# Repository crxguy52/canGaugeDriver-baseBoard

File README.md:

Hardware to to use [CANBed FD](https://www.seeedstudio.com/CANBed-FD-Arduino-CAN-FD-Development-Kit-p-4724.html) to read CAN data and drive gauges on a NB Miata

Used in conjunction with the [software](https://github.com/crxguy52/canGaugeDriver)

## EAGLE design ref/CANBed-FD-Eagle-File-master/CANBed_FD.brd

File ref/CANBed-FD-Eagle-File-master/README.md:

# CANBed-FD-Eagle-File
EAGLE FILE FOR CANBED-FD

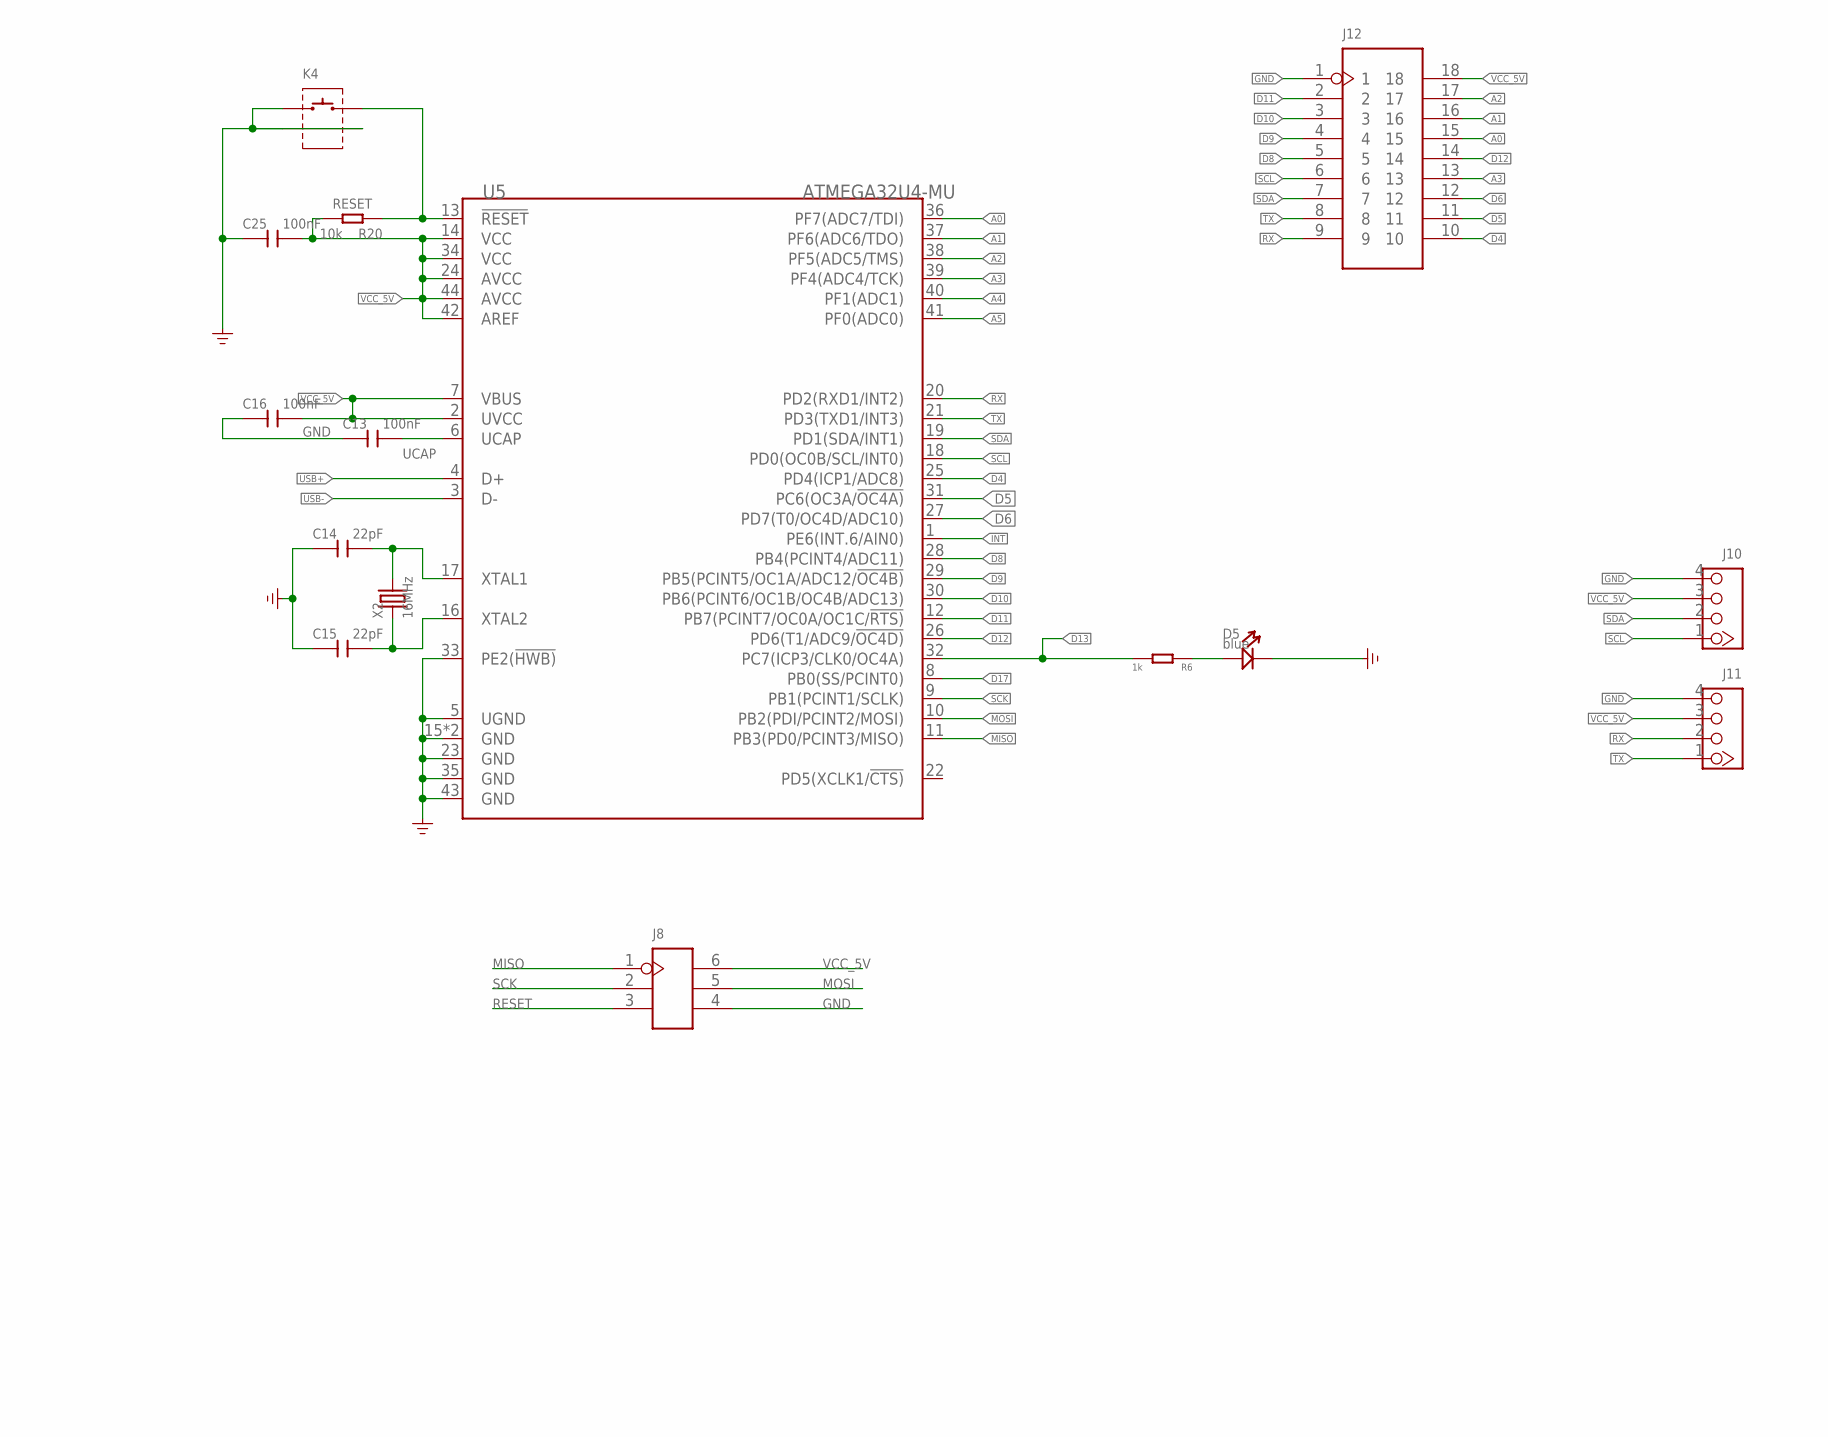
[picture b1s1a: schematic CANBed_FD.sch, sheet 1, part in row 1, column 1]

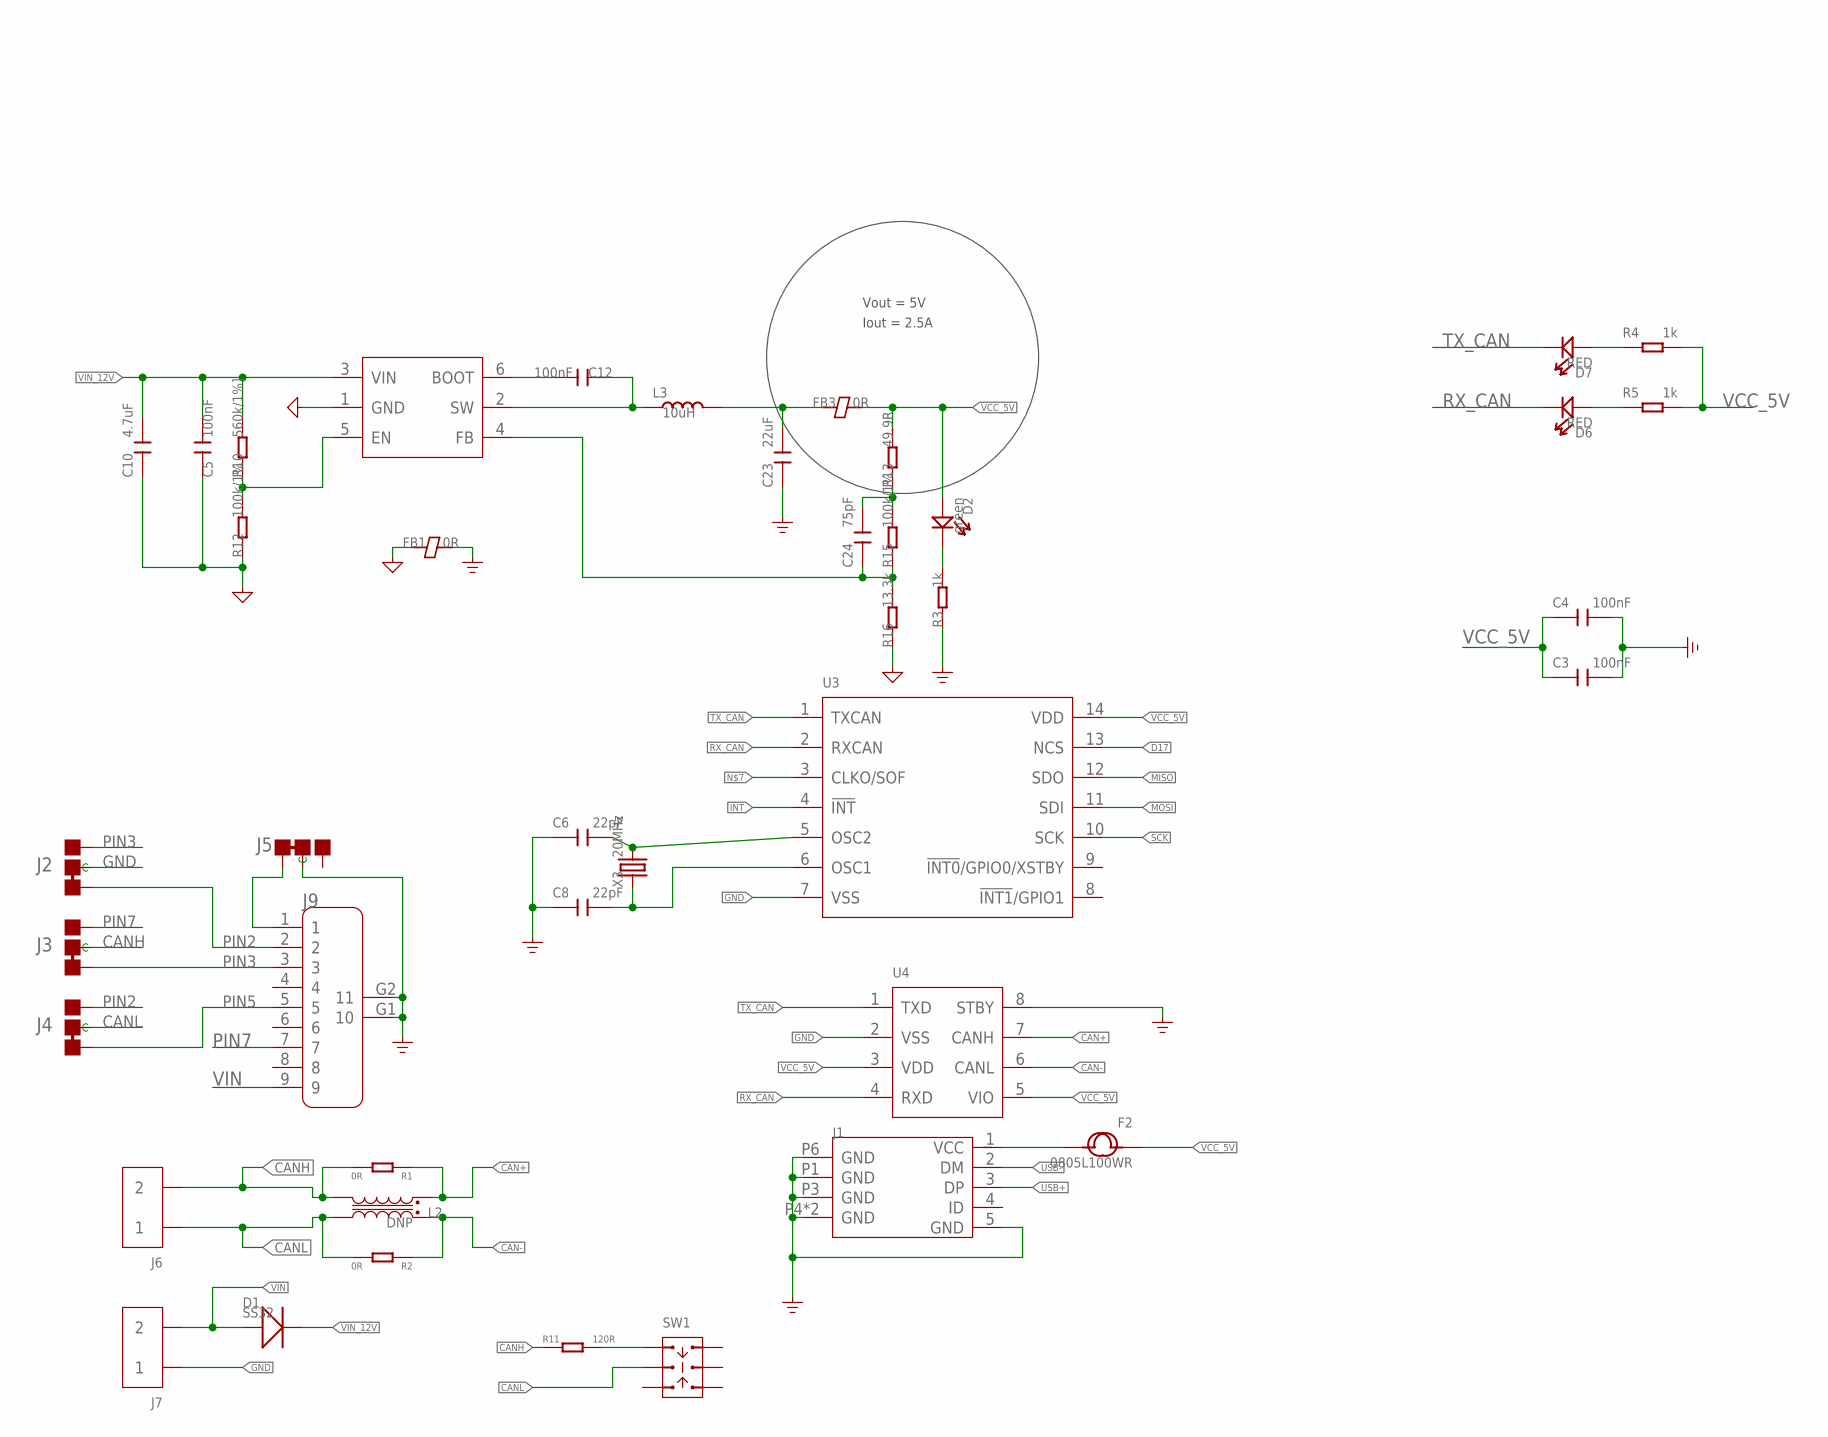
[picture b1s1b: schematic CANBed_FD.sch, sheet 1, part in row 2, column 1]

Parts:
C3, C4, C5, C12, C13, C16, C25: 100nF; C0603
C6, C8, C14, C15: 22pF; C0603
C10: 4.7uF; C1206
C23: 22uF; C1206
C24: 75pF; C0603
D1: SS32; DO-214AC
D2: green; LED-0603
D5: blue; LED-0603
D6, D7: RED; LED-0603
F2: 0805L100WR; F0805
FB1, FB3: 0R; F0805
J1: MICRO-USB5+4P-320010050; MICRO-USB5+5P-SMD-0.65-7.2X5.06MM
J2, J3, J4, J5: JUMPER-3P-SHORT; 3P-SMD-SHORT
J6, J7: SCREW-TERMINAL-2P'5.08'; H2-5.0-10.5X8.0MM
J8: HEADER-2X3P-2.54; H2X3-2.54
J9: DB9'MEAL'; DB9-MEAL
J10, J11: 320110033; HW4-2.0
J12: HEADER-2X9P-2.54; H2X9-2.54
K4: BUTTON-2+2P; SW2+2P-7.7X2.75X3.95MM
L2: DNP; INT4-0.85-2X1.25X1.2MM
L3: 10uH; INT2-SMD-6.6X7.1X3MM
R1, R2: 0R; R0603
R3, R4, R5, R6: 1k; R0603
R10: 560k/1%]; R0603
R11: 120R; R0603
R12, R15: 100k/1%; R0603
R13: 49.9R; R0603
R16: 13.3k; R0603
R20: 10k; R0603
SW1: SWITCH-2CH-6P-311010004; SW6-2.54-9.0X3.5X3.2+2.0MM
U3: CONTROLLER-MCP2517FD; SOIC14-1.27-8.6X3.9MM
U4: TRANSCEIVER-MCP2542; SOIC8-1.27-5X4MM
U5: ATMEGA32U4-MU; QFN44
U$11: PMIC-TPS54302; SOT-23-6
X2: 16MHz; HC49US
X3: 20MHz; HC49US

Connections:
A0: J12.15, U5.36 (PF7(ADC7/TDI))
A1: J12.16, U5.37 (PF6(ADC6/TDO))
A2: J12.17, U5.38 (PF5(ADC5/TMS))
A3: J12.13, U5.39 (PF4(ADC4/TCK))
A4: U5.40 (PF1(ADC1))
A5: U5.41 (PF0(ADC0))
AGND: C5.1, C10.1, FB1.1, R12.1, R16.1, U$11.1 (GND)
CAN+: L2.4, R1.1, U4.7 (CANH)
CAN-: L2.1, R2.1, U4.6 (CANL)
CANH: J3.MM (C), J6.2, L2.3, R1.2, R11.1
CANL: J4.MM (C), J6.1, L2.2, R2.2, SW1.COM1
D4: J12.10, U5.25 (PD4(ICP1/ADC8))
D5: J12.11, U5.31 (PC6(OC3A/!OC4A))
D6: J12.12, U5.27 (PD7(T0/OC4D/ADC10))
D8: J12.5, U5.28 (PB4(PCINT4/ADC11))
D9: J12.4, U5.29 (PB5(PCINT5/OC1A/ADC12/!OC4B))
D10: J12.3, U5.30 (PB6(PCINT6/OC1B/OC4B/ADC13))
D11: J12.2, U5.12 (PB7(PCINT7/OC0A/OC1C/!RTS))
D12: J12.14, U5.26 (PD6(T1/ADC9/!OC4D))
D13: R6.2, U5.32 (PC7(ICP3/CLK0/OC4A))
D17: U3.13 (NCS), U5.8 (PB0(SS/PCINT0))
EXT_PWR: F2.2, J1.1 (VCC)
GND: C3.2, C4.2, C6.1, C8.1, C13.1, C14.1, C15.1, C16.1, C23.1, C25.1, D5.-, FB1.2, J1.5 (GND), J1.P1 (GND), J1.P3 (GND), J1.P4 (GND), J1.P5 (GND), J1.P6 (GND), J2.MM (C), J5.MM (C), J7.1, J8.4, J9.G1 (10), J9.G2 (11), J10.4, J11.4, J12.1, K4.1, K4.S1, K4.S2, R3.1, U3.7 (VSS), U4.2 (VSS), U4.8 (STBY), U5.5 (UGND), U5.15 (GND), U5.23 (GND), U5.33 (PE2(!HWB)), U5.35 (GND), U5.43 (GND), U5.TAB (GND)
INT: U3.4 (!INT), U5.1 (PE6(INT.6/AIN0))
MISO: J8.1, U3.12 (SDO), U5.11 (PB3(PD0/PCINT3/MISO))
MOSI: J8.5, U3.11 (SDI), U5.10 (PB2(PDI/PCINT2/MOSI))
unnamed: D2.-, R3.2
unnamed: D7.+, R4.1
unnamed: R10.1, R12.2, U$11.5 (EN)
unnamed: C14.2, U5.17 (XTAL1), X2.2
unnamed: D5.+, R6.1
unnamed: C6.2, U3.5 (OSC2), X3.2
unnamed: C12.1, L3.1, U$11.2 (SW)
unnamed: C15.2, U5.16 (XTAL2), X2.1
unnamed: J5.11 (L), J9.1
unnamed: C12.2, U$11.6 (BOOT)
unnamed: D6.+, R5.1
unnamed: R11.2, SW1.CH1A
unnamed: C8.2, U3.6 (OSC1), X3.1
unnamed: C23.2, FB3.1, L3.2
unnamed: C24.2, R13.1, R15.2
unnamed: C24.1, R15.1, R16.2, U$11.4 (FB)
PIN2: J2.11 (L), J4.00 (R), J9.2
PIN3: J2.00 (R), J3.11 (L), J9.3
PIN5: J4.11 (L), J9.5
PIN7: J3.00 (R), J9.7
RESET: J8.3, K4.2, R20.1, U5.13 (!RESET)
RX: J11.2, J12.9, U5.20 (PD2(RXD1/INT2))
RX_CAN: D6.-, U3.2 (RXCAN), U4.4 (RXD)
SCK: J8.2, U3.10 (SCK), U5.9 (PB1(PCINT1/SCLK))
SCL: J10.1, J12.6, U5.18 (PD0(OC0B/SCL/INT0))
SDA: J10.2, J12.7, U5.19 (PD1(SDA/INT1))
TX: J11.1, J12.8, U5.21 (PD3(TXD1/INT3))
TX_CAN: D7.-, U3.1 (TXCAN), U4.1 (TXD)
UCAP: C13.2, U5.6 (UCAP)
USB+: J1.3 (DP), U5.4 (D+)
USB-: J1.2 (DM), U5.3 (D-)
VCC_5V: C3.1, C4.1, C16.2, C25.2, D2.+, F2.1, FB3.2, J8.6, J10.3, J11.3, J12.18, R4.2, R5.2, R13.2, R20.2, U3.14 (VDD), U4.3 (VDD), U4.5 (VIO), U5.2 (UVCC), U5.7 (VBUS), U5.14 (VCC), U5.24 (AVCC), U5.34 (VCC), U5.42 (AREF), U5.44 (AVCC)
VIN: D1.1 (+), J7.2, J9.9
VIN_12V: C5.2, C10.2, D1.2 (-), R10.2, U$11.3 (VIN)

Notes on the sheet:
Vout = 5V
Iout = 2.5A

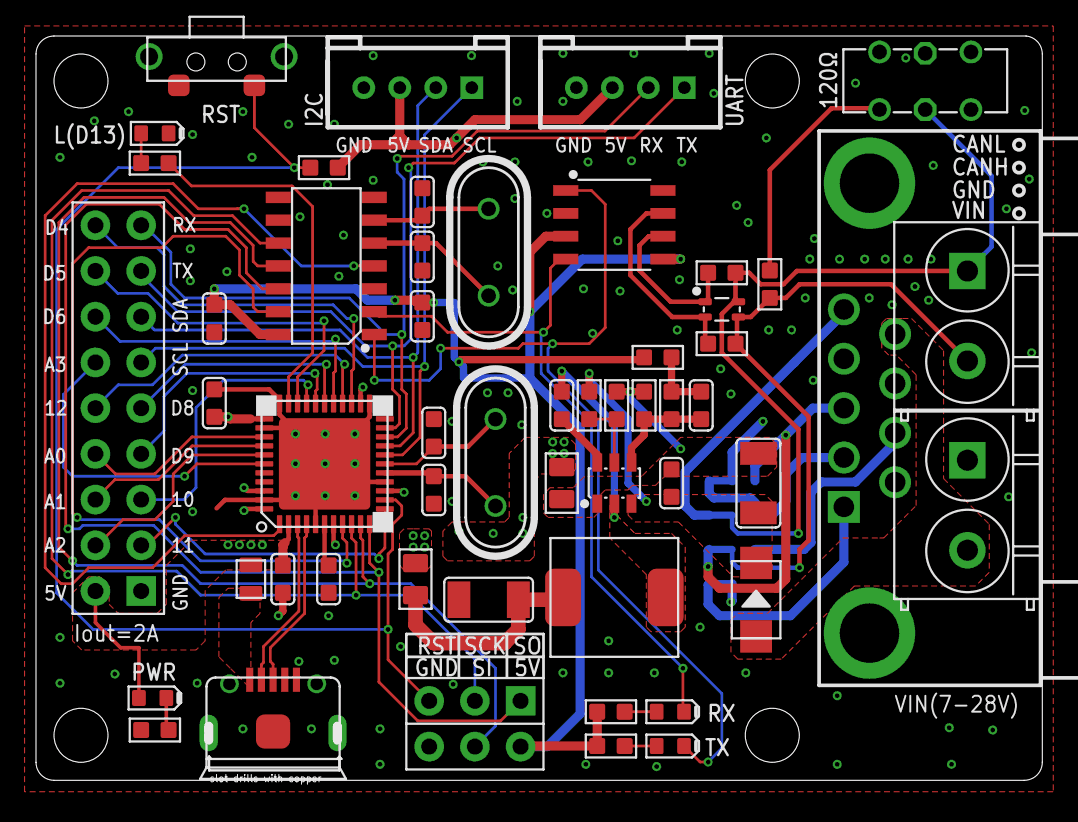
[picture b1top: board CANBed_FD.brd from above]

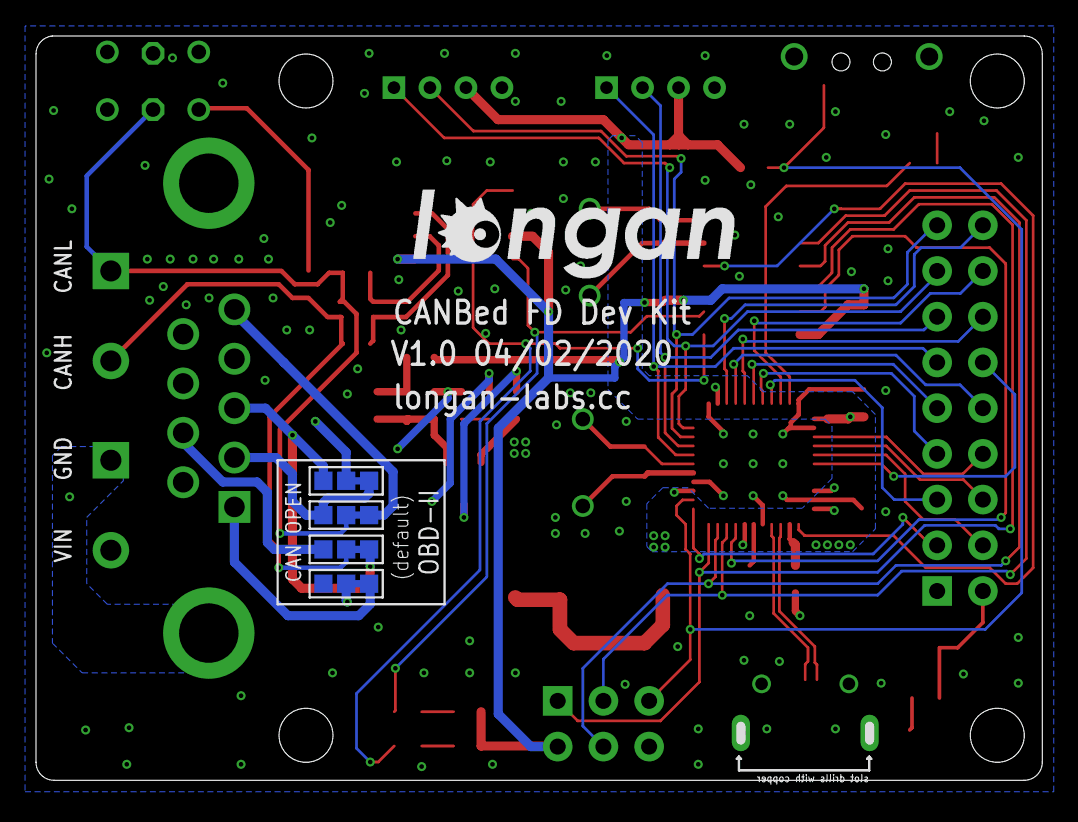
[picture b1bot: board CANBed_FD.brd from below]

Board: 2 copper layers, 55.9 x 41.4 mm, 58 parts (5 on the bottom side), 58 nets.

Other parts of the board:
U$12: LONGAN-SILK-SMALL
